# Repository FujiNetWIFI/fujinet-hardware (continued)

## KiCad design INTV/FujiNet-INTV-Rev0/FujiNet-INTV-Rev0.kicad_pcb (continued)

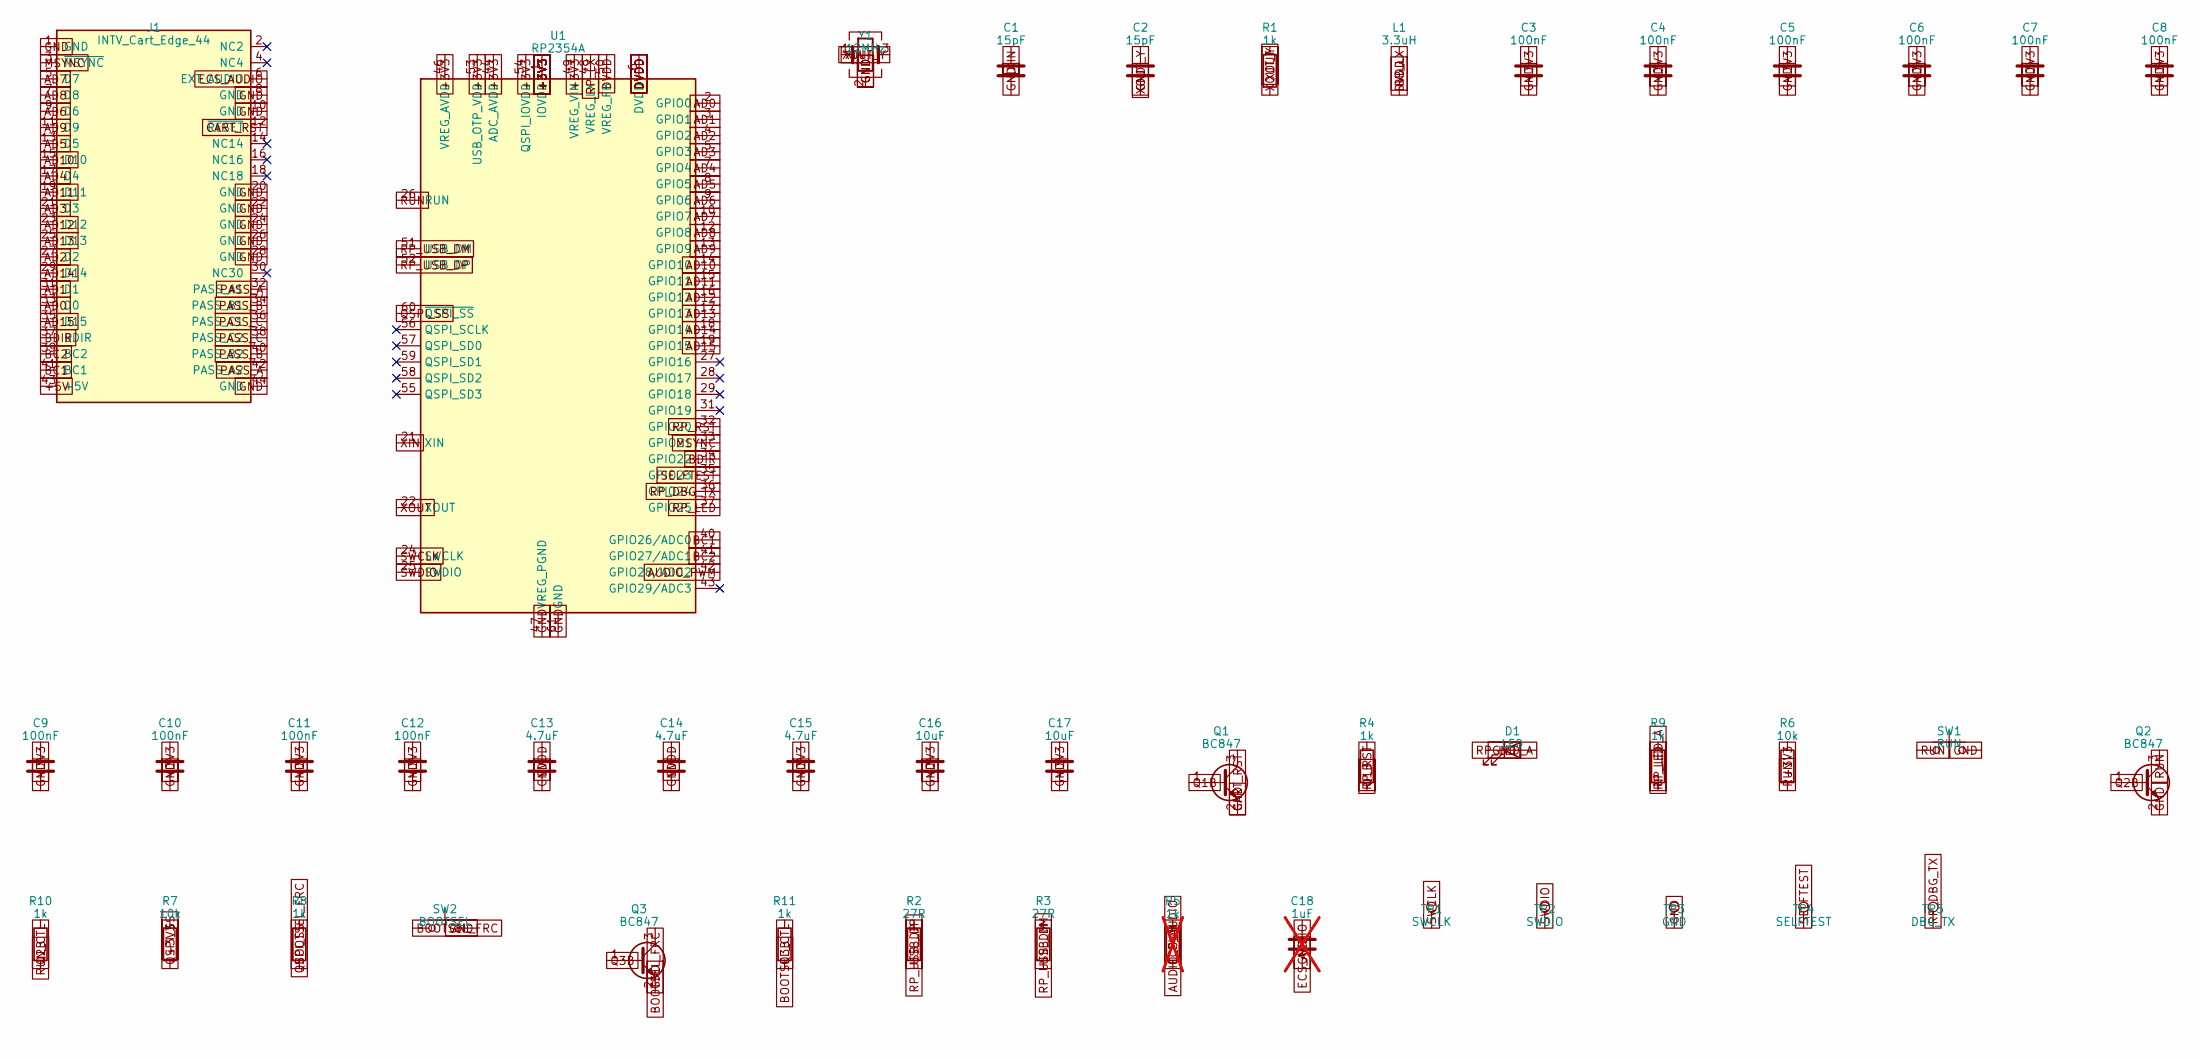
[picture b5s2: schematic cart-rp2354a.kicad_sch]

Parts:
C1, C2: 15pF; C_0603_1608Metric
C3, C4, C5, C6, C7, C8, C9, C10, C11, C12: 100nF; C_0603_1608Metric
C13, C14, C15: 4.7uF; C_0603_1608Metric
C16, C17: 10uF; C_0603_1608Metric; LCSC C19702
C18: 1uF; C_0603_1608Metric; not fitted
D1: LED; LED_0603_1608Metric
J1: INTV_Cart_Edge_44; MPN card edge, 2x22, 2.54mm
L1: 3.3uH; L_2016Metric; MPN AOTA-B201610S3R3-101-T; LCSC C42411119
Q1, Q2, Q3: BC847; SOT-23; LCSC C8598
R1, R4, R8, R9, R10, R11: 1k; R_0603_1608Metric
R2, R3: 27R; R_0603_1608Metric
R5: 1k; R_0603_1608Metric; not fitted
R6, R7: 10k; R_0603_1608Metric
SW1: RUN; SW_SPST_TL3342
SW2: BOOTSEL; SW_SPST_TL3342
TP1: SWCLK; TestPoint_Pad_D1.5mm
TP2: SWDIO; TestPoint_Pad_D1.5mm
TP3: GND; TestPoint_Pad_D1.5mm
TP4: SELFTEST; TestPoint_Pad_D1.5mm
TP5: DBG_TX; TestPoint_Pad_D1.5mm
U1: RP2354A; QFN-60-1EP_7x7mm_P0.4mm_EP3.4x3.4mm; MPN RP2354A; LCSC C41378174
Y1: 12MHz; Crystal_SMD_3225-4Pin_3.2x2.5mm; MPN ABM8-272-T3; LCSC C20625731

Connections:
+3V3: C3.1, C4.1, C5.1, C6.1, C7.1, C8.1, C9.1, C10.1, C11.1, C12.1, C15.1, C16.1, C17.1, R6.1, R7.1, U1.1 (IOVDD), U1.11 (IOVDD), U1.20 (IOVDD), U1.30 (IOVDD), U1.38 (IOVDD), U1.44 (ADC_AVDD), U1.45 (IOVDD), U1.46 (VREG_AVDD), U1.49 (VREG_VIN), U1.53 (USB_OTP_VDD), U1.54 (QSPI_IOVDD); also elsewhere on the board
+5V: J1.43 (+5V); also elsewhere on the board
AD0: J1.33 (D0), U1.2 (GPIO0)
AD1: J1.31 (D1), U1.3 (GPIO1)
AD2: J1.27 (D2), U1.4 (GPIO2)
AD3: J1.21 (D3), U1.5 (GPIO3)
AD4: J1.17 (D4), U1.7 (GPIO4)
AD5: J1.13 (D5), U1.8 (GPIO5)
AD6: J1.9 (D6), U1.9 (GPIO6)
AD7: J1.5 (D7), U1.10 (GPIO7)
AD8: J1.7 (D8), U1.12 (GPIO8)
AD9: J1.11 (D9), U1.13 (GPIO9)
AD10: J1.15 (D10), U1.14 (GPIO10)
AD11: J1.19 (D11), U1.15 (GPIO11)
AD12: J1.23 (D12), U1.16 (GPIO12)
AD13: J1.25 (D13), U1.17 (GPIO13)
AD14: J1.29 (D14), U1.18 (GPIO14)
AD15: J1.35 (D15), U1.19 (GPIO15)
AUDIO_PWM: R5.1, U1.42 (GPIO28/ADC2)
BC1: J1.41 (BC1), U1.40 (GPIO26/ADC0)
BC2: J1.39 (BC2), U1.41 (GPIO27/ADC1)
BDIR: J1.37 (BDIR), U1.34 (GPIO22)
BOOTSEL_CTL: R11.1; also elsewhere on the board
BOOTSEL_FRC: Q3.3 (C), R8.2, SW2.1
CART_RST: J1.12 (~RESET), Q1.3 (C)
DVDD: C13.1, C14.1, L1.2, U1.6 (DVDD), U1.23 (DVDD), U1.39 (DVDD), U1.50 (VREG_FB)
ECS_AUDIO: C18.1, J1.6 (EXT_AUDIO), R5.2
GND: C1.2, C2.2, C3.2, C4.2, C5.2, C6.2, C7.2, C8.2, C9.2, C10.2, C11.2, C12.2, C13.2, C14.2, C15.2, C16.2, C17.2, C18.2, D1.1 (K), J1.1 (GND), J1.8 (GND), J1.10 (GND), J1.20 (GND), J1.22 (GND), J1.24 (GND), J1.26 (GND), J1.28 (GND), J1.44 (GND), Q1.2 (E), Q2.2 (E), Q3.2 (E), SW1.2, SW2.2, TP3.1, U1.47 (VREG_PGND), U1.61 (GND), Y1.2 (G), Y1.4 (G); also elsewhere on the board
MSYNC: J1.3 (~MSYNC), U1.33 (GPIO21)
PASS_A: J1.32 (PASS_A1), J1.42 (PASS_A2)
PASS_B: J1.34 (PASS_B1), J1.40 (PASS_B2)
PASS_C: J1.36 (PASS_C1), J1.38 (PASS_C2)
Q1B: Q1.1 (B), R4.2
Q2B: Q2.1 (B), R10.2
Q3B: Q3.1 (B), R11.2
QSPI_SS: R7.2, R8.1, U1.60 (~QSPI_SS)
RP_DBG_TX: TP5.1, U1.36 (GPIO24)
RP_LED: R9.1, U1.37 (GPIO25)
RP_LED_A: D1.2 (A), R9.2
RP_LX: L1.1, U1.48 (VREG_LX)
RP_RST: R4.1, U1.32 (GPIO20)
RP_USB_DM: R3.1, U1.51 (USB_DM)
RP_USB_DP: R2.1, U1.52 (USB_DP)
RUN: Q2.3 (C), R6.2, SW1.1, U1.26 (RUN)
RUN_CTL: R10.1; also elsewhere on the board
SELFTEST: TP4.1, U1.35 (GPIO23)
SWCLK: TP1.1, U1.24 (SWCLK)
SWDIO: TP2.1, U1.25 (SWDIO)
USB_DM: R3.2; also elsewhere on the board
USB_DP: R2.2; also elsewhere on the board
XIN: C1.1, U1.21 (XIN), Y1.1
XOUT: R1.1, U1.22 (XOUT)
XOUT_Y: C2.1, R1.2, Y1.3

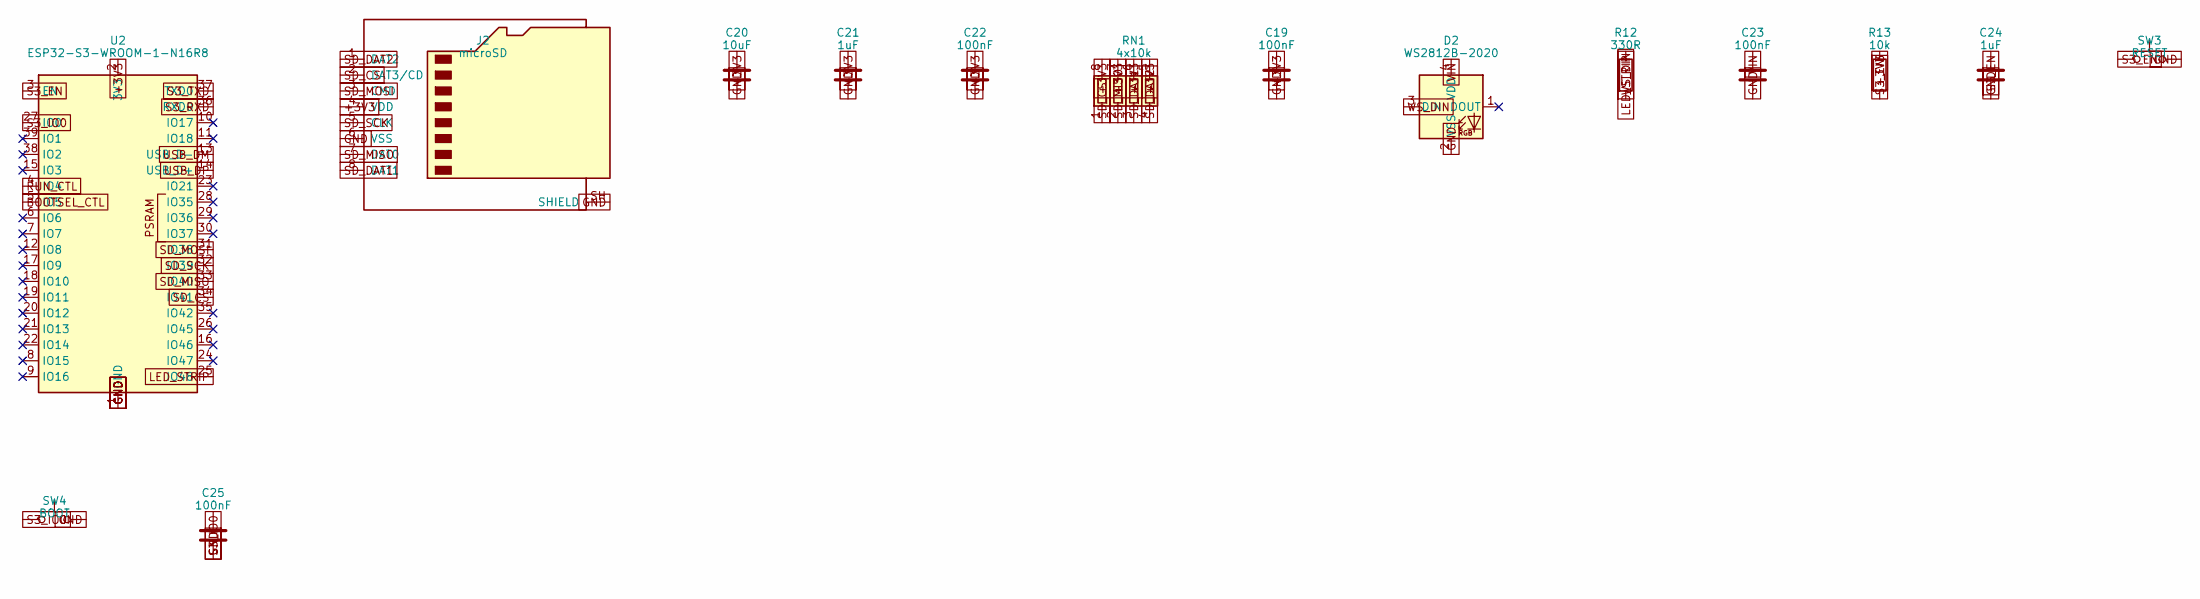
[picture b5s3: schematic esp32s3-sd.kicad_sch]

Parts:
C19, C22, C23, C25: 100nF; C_0603_1608Metric
C20: 10uF; C_0603_1608Metric; LCSC C19702
C21, C24: 1uF; C_0603_1608Metric
D2: WS2812B-2020; LED_WS2812B-2020_PLCC4_2.0x2.0mm; MPN WS2812B-2020; LCSC C5149201
J2: microSD; microSD_SUNTECH_ST-TF-003A; MPN SUNTECH ST-TF-003A
R12: 330R; R_0603_1608Metric
R13: 10k; R_0603_1608Metric
RN1: 4x10k; R_Array_Convex_4x0603
SW3: RESET; SW_SPST_TL3342
SW4: BOOT; SW_SPST_TL3342
U2: ESP32-S3-WROOM-1-N16R8; ESP32-S3-WROOM-1; MPN ESP32-S3-WROOM-1-N16R8; LCSC C2913202

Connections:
+3V3: C19.1, C20.1, C21.1, C22.1, J2.4 (VDD), R13.1, RN1.5 (R4.2), RN1.6 (R3.2), RN1.7 (R2.2), RN1.8 (R1.2), U2.2 (3V3); also elsewhere on the board
BOOTSEL_CTL: U2.5 (IO5); also elsewhere on the board
GND: C19.2, C20.2, C21.2, C22.2, C23.2, C24.2, C25.2, D2.2 (VSS), J2.6 (VSS), J2.SH (SHIELD), SW3.2, SW4.2, U2.1 (GND), U2.40 (GND), U2.41 (GND); also elsewhere on the board
LED_STRIP: R12.1, U2.25 (IO48)
RUN_CTL: U2.4 (IO4); also elsewhere on the board
S3_EN: C24.1, R13.2, SW3.1, U2.3 (EN); also elsewhere on the board
S3_IO0: C25.1, SW4.1, U2.27 (IO0); also elsewhere on the board
S3_RXD: U2.36 (RXD0); also elsewhere on the board
S3_TXD: U2.37 (TXD0); also elsewhere on the board
SD_CS: J2.2 (DAT3/CD), RN1.1 (R1.1), U2.34 (IO41)
SD_DAT1: J2.8 (DAT1), RN1.3 (R3.1)
SD_DAT2: J2.1 (DAT2), RN1.4 (R4.1)
SD_MISO: J2.7 (DAT0), RN1.2 (R2.1), U2.33 (IO40)
SD_MOSI: J2.3 (CMD), U2.31 (IO38)
SD_SCK: J2.5 (CLK), U2.32 (IO39)
USB_DM: U2.13 (USB_D-); also elsewhere on the board
USB_DP: U2.14 (USB_D+); also elsewhere on the board
VIN: C23.1, D2.4 (VDD); also elsewhere on the board
WS_DIN: D2.3 (DIN), R12.2

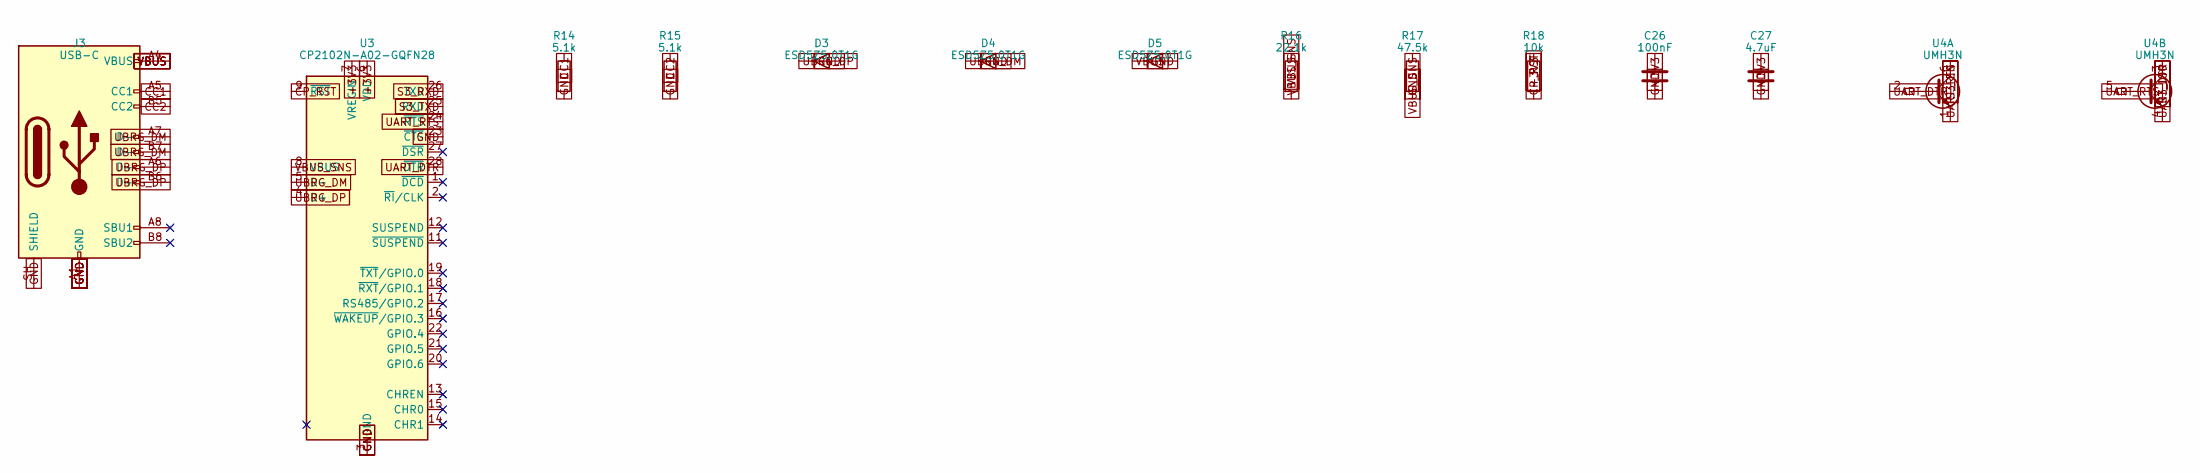
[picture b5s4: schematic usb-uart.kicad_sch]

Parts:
C26: 100nF; C_0603_1608Metric
C27: 4.7uF; C_0603_1608Metric
D3, D4, D5: ESD5Z5.0T1G; D_SOD-523; LCSC C316061
J3: USB-C; USB_C_Receptacle_HRO_TYPE-C-31-M-12; MPN HRO TYPE-C-31-M-12; LCSC C5178539
R14, R15: 5.1k; R_0603_1608Metric
R16: 22.1k; R_0603_1608Metric
R17: 47.5k; R_0603_1608Metric
R18: 10k; R_0603_1608Metric
U3: CP2102N-A02-GQFN28; QFN-28-1EP_5x5mm_P0.5mm_EP3.35x3.35mm; MPN CP2102N-A02-GQFN28R
U4: UMH3N; SOT-363_SC-70-6; LCSC C123008

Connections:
+3V3: C26.1, C27.1, R18.1, U3.6 (VDD), U3.7 (VREGIN); also elsewhere on the board
CC1: J3.A5 (CC1), R14.1
CC2: J3.B5 (CC2), R15.1
CP_RST: R18.2, U3.9 (~RST)
GND: C26.2, C27.2, D3.2 (A), D4.2 (A), D5.2 (A), J3.A1 (GND), J3.A12 (GND), J3.B1 (GND), J3.B12 (GND), J3.SH (SHIELD), R14.2, R15.2, R17.2, U3.3 (GND), U3.23 (~CTS), U3.29 (GND); also elsewhere on the board
S3_EN: U4.6 (C1); also elsewhere on the board
S3_IO0: U4.3 (C2); also elsewhere on the board
S3_RXD: U3.26 (TXD); also elsewhere on the board
S3_TXD: U3.25 (RXD); also elsewhere on the board
UART_DTR: U3.28 (~DTR), U4.2 (B1), U4.4 (E2)
UART_RTS: U3.24 (~RTS), U4.1 (E1), U4.5 (B2)
UBRG_DM: D4.1 (K), J3.A7 (D-), J3.B7 (D-), U3.5 (D-)
UBRG_DP: D3.1 (K), J3.A6 (D+), J3.B6 (D+), U3.4 (D+)
VBUS: D5.1 (K), J3.A4 (VBUS), J3.A9 (VBUS), J3.B4 (VBUS), J3.B9 (VBUS), R16.1; also elsewhere on the board
VBUS_SNS: R16.2, R17.1, U3.8 (VBUS)

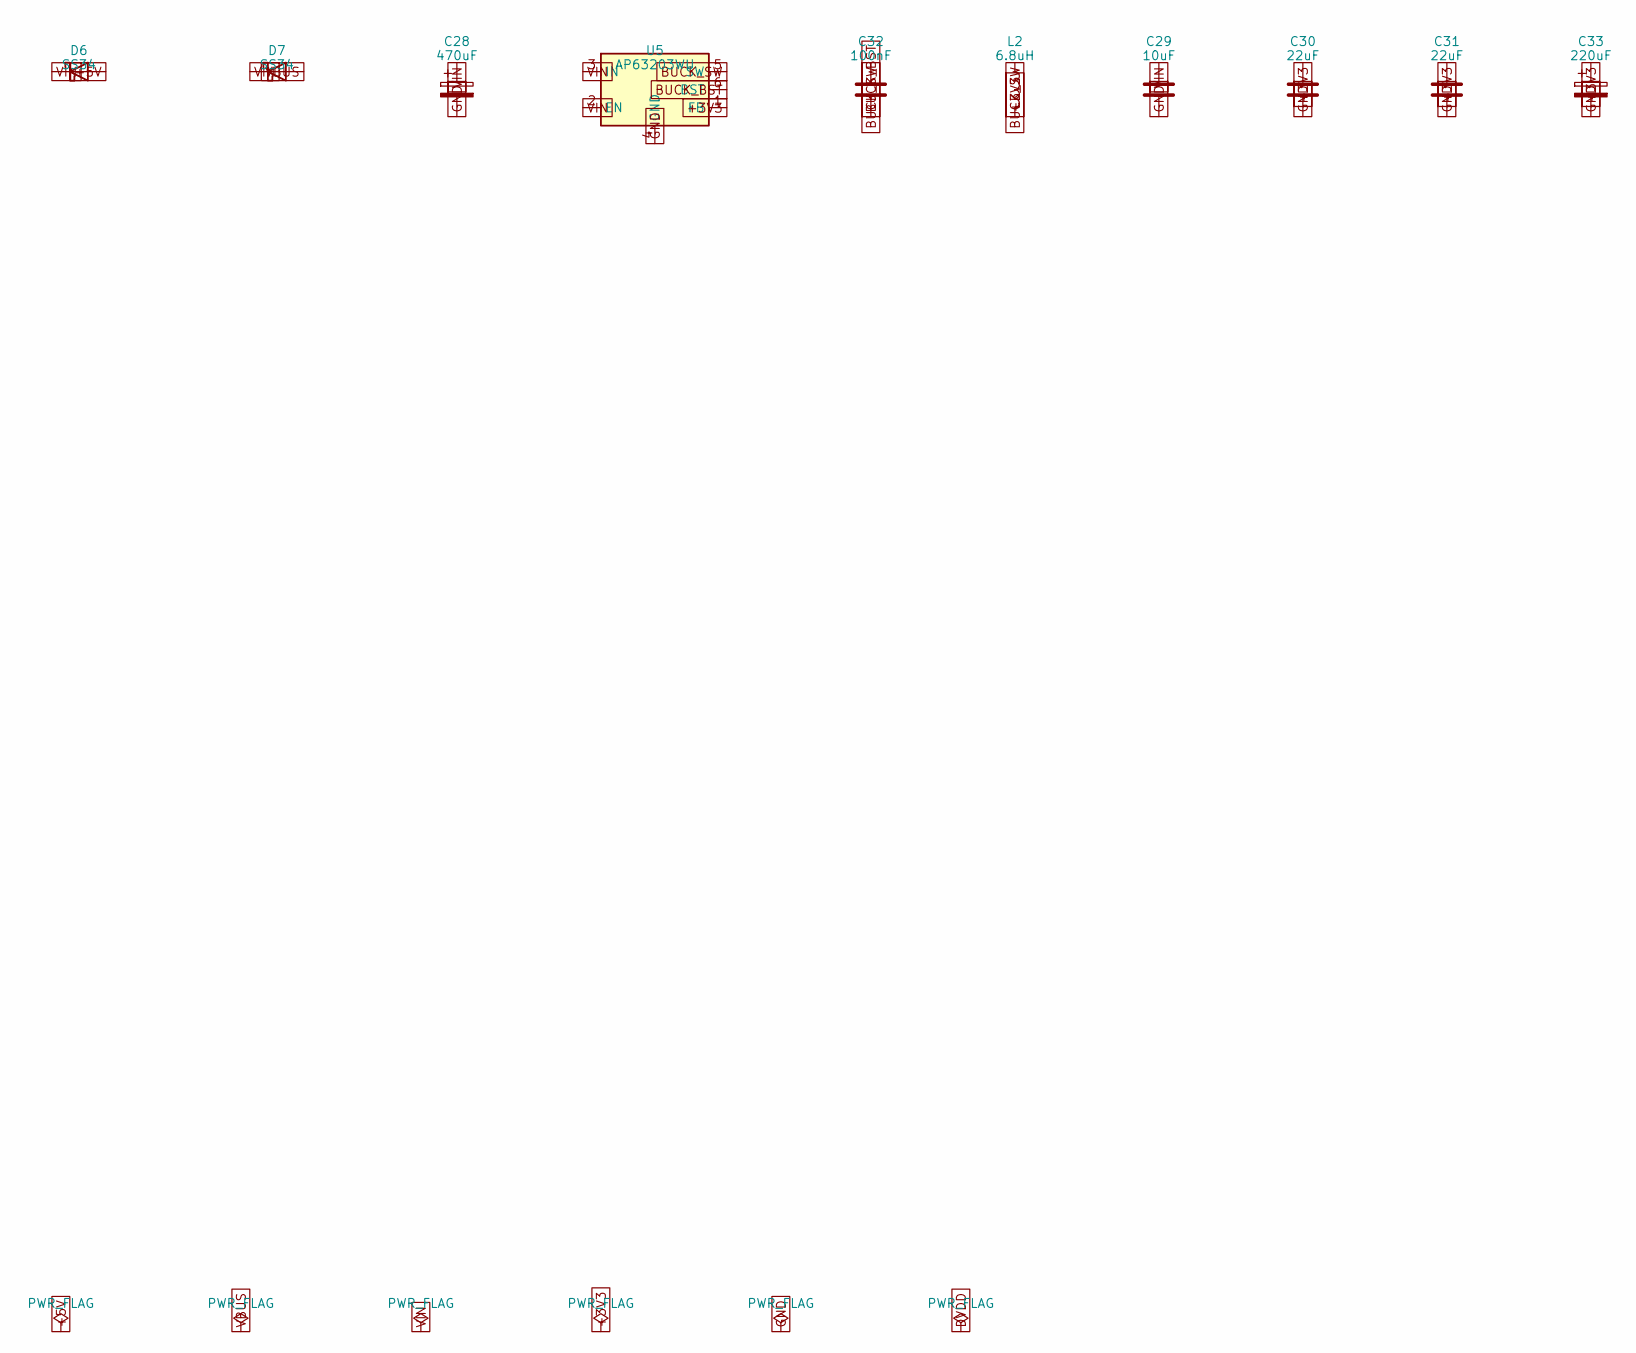
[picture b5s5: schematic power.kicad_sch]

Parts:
C28: 470uF; CP_EIA-7343-31_Kemet-D; MPN 6.3V polymer, 7343
C29: 10uF; C_0805_2012Metric
C30, C31: 22uF; C_0805_2012Metric; LCSC C45783
C32: 100nF; C_0603_1608Metric
C33: 220uF; CP_EIA-7343-31_Kemet-D; MPN 6.3V polymer, 7343
D6, D7: SS34; D_SMA; LCSC C8678
L2: 6.8uH; L_Sunlord_SWPA4030S; MPN 6.8uH >=2.5A shielded 4030
U5: AP63203WU; TSOT-23-6; MPN AP63203WU-7; LCSC C965680

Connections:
+3V3: C30.1, C31.1, C33.1, L2.2, U5.1 (FB); also elsewhere on the board
+5V: D6.2 (A); also elsewhere on the board
BUCK_BST: C32.2, U5.6 (BST)
BUCK_SW: C32.1, L2.1, U5.5 (SW)
GND: C28.2, C29.2, C30.2, C31.2, C33.2, U5.4 (GND); also elsewhere on the board
VBUS: D7.2 (A); also elsewhere on the board
VIN: C28.1, C29.1, D6.1 (K), D7.1 (K), U5.2 (EN), U5.3 (IN); also elsewhere on the board

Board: 4 copper layers, 84 parts (5 on the bottom side), 77 nets, no tracks yet.

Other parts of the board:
H1, H2: MountingHole_5.4mm_NPTH

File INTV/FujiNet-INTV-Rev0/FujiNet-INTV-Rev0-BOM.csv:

"Refs","Value","Footprint","MPN","LCSC","Description","DNP"
"C1,C2","15pF","FujiNet-INTV:C_0603_1608Metric","","","crystal load",""
"C3,C4,C5,C6,C7,C8,C9,C10,C11,C12,C19,C22,C23,C25,C26,C32","100nF","FujiNet-INTV:C_0603_1608Metric","","","IO0 debounce,SD VDD decoupling,U1 decoupling,U2 decoupling,U3 decoupling,WS2812 decoupling,bootstrap",""
"C13,C14,C15,C27","4.7uF","FujiNet-INTV:C_0603_1608Metric","","","DVDD bulk,U3 bulk,VREG_VIN bulk",""
"C16,C17,C20","10uF","FujiNet-INTV:C_0603_1608Metric","","C19702","3V3 bulk near U1,U2 bulk",""
"C18","1uF","FujiNet-INTV:C_0603_1608Metric","","","ECS audio filter (DNP)","DNP"
"C21,C24","1uF","FujiNet-INTV:C_0603_1608Metric","","","EN reset delay,U2 decoupling",""
"C28","470uF","FujiNet-INTV:CP_EIA-7343-31_Kemet-D","6.3V polymer, 7343","","VIN bulk",""
"C29","10uF","FujiNet-INTV:C_0805_2012Metric","","","buck input",""
"C30,C31","22uF","FujiNet-INTV:C_0805_2012Metric","","C45783","buck output",""
"C33","220uF","FujiNet-INTV:CP_EIA-7343-31_Kemet-D","6.3V polymer, 7343","","3V3 bulk (S3 WiFi bursts)",""
"D1","LED","FujiNet-INTV:LED_0603_1608Metric","","","RP activity LED (light pipe)",""
"D2","WS2812B-2020","FujiNet-INTV:LED_WS2812B-2020_PLCC4_2.0x2.0mm","WS2812B-2020","C5149201","status LED (fujiversal LED_STRIP, 1px)",""
"D3,D4,D5","ESD5Z5.0T1G","FujiNet-INTV:D_SOD-523","","C316061","ESD, USB D+,ESD, USB D-,ESD, VBUS",""
"D6,D7","SS34","FujiNet-INTV:D_SMA","","C8678","USB VBUS OR-ing,console 5V OR-ing / backfeed block",""
"J1","INTV_Cart_Edge_44","FujiNet-INTV:INTV_Cart_Edge_44","card edge, 2x22, 2.54mm","","Intellivision cartridge edge (geometry per PiNTY CARD)",""
"J2","microSD","FujiNet-INTV:microSD_SUNTECH_ST-TF-003A","SUNTECH ST-TF-003A","","push-push microSD (footprint per CoCo-FujiNet-Rev0000)",""
"J3","USB-C","FujiNet-INTV:USB_C_Receptacle_HRO_TYPE-C-31-M-12","HRO TYPE-C-31-M-12","C5178539","USB-C 16P (UART/flash port)",""
"L1","3.3uH","FujiNet-INTV:L_2016Metric","AOTA-B201610S3R3-101-T","C42411119","RP2354A core VREG inductor",""
"L2","6.8uH","FujiNet-INTV:L_Sunlord_SWPA4030S","6.8uH >=2.5A shielded 4030","","buck inductor (AP63203 datasheet)",""
"Q1,Q2,Q3","BC847","FujiNet-INTV:SOT-23","","C8598","BOOTSEL force (S3 GPIO5, Hi-Z idle),RUN force (S3 GPIO4, Hi-Z idle),console /RESET open-collector",""
"R1,R4,R8,R9,R10,R11","1k","FujiNet-INTV:R_0603_1608Metric","","","BOOTSEL series,LED series,Q1 base,Q2 base,Q3 base,XOUT series (RP2350 design guide)",""
"R2,R3","27R","FujiNet-INTV:R_0603_1608Metric","","","USB D+ series,USB D- series",""
"R5","1k","FujiNet-INTV:R_0603_1608Metric","","","ECS audio PWM series (DNP)","DNP"
"R6,R7,R13,R18","10k","FujiNet-INTV:R_0603_1608Metric","","","CP2102N /RST pull-up,EN pull-up,QSPI_SS/BOOTSEL pull-up,RUN pull-up",""
"R12","330R","FujiNet-INTV:R_0603_1608Metric","","","WS2812 data series",""
"R14,R15","5.1k","FujiNet-INTV:R_0603_1608Metric","","","CC1 pull-down (UFP),CC2 pull-down (UFP)",""
"R16","22.1k","FujiNet-INTV:R_0603_1608Metric","","","VBUS sense divider hi",""
"R17","47.5k","FujiNet-INTV:R_0603_1608Metric","","","VBUS sense divider lo",""
"RN1","4x10k","FujiNet-INTV:R_Array_Convex_4x0603","","","SD pull-ups",""
"SW1","RUN","FujiNet-INTV:SW_SPST_TL3342","","","RP2354A reset button",""
"SW2","BOOTSEL","FujiNet-INTV:SW_SPST_TL3342","","","RP2354A BOOTSEL button",""
"SW3","RESET","FujiNet-INTV:SW_SPST_TL3342","","","ESP32 reset button",""
"SW4","BOOT","FujiNet-INTV:SW_SPST_TL3342","","","ESP32 IO0 boot button",""
"U1","RP2354A","FujiNet-INTV:QFN-60-1EP_7x7mm_P0.4mm_EP3.4x3.4mm","RP2354A","C41378174","RP2350A + 2MB stacked QSPI flash, QFN-60",""
"U2","ESP32-S3-WROOM-1-N16R8","FujiNet-INTV:ESP32-S3-WROOM-1","ESP32-S3-WROOM-1-N16R8","C2913202","16MB QIO flash / 8MB octal PSRAM (IO35-37 NC)",""
"U3","CP2102N-A02-GQFN28","FujiNet-INTV:QFN-28-1EP_5x5mm_P0.5mm_EP3.35x3.35mm","CP2102N-A02-GQFN28R","","USB-UART bridge (DevKitC-1 UART port)",""
"U4","UMH3N","FujiNet-INTV:SOT-363_SC-70-6","","C123008","auto-program: DTR/RTS -> EN/IO0 (DevKitC-1 circuit)",""
"U5","AP63203WU","FujiNet-INTV:TSOT-23-6","AP63203WU-7","C965680","3.3V/2A sync buck (FB tied to VOUT: fixed 3.3V version)",""
"Y1","12MHz","FujiNet-INTV:Crystal_SMD_3225-4Pin_3.2x2.5mm","ABM8-272-T3","C20625731","12MHz 3225, CL=10pF (per PiNTY)",""

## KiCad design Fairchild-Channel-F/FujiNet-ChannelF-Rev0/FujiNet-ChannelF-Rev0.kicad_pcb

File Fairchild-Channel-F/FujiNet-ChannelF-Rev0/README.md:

# FujiNet-ChannelF Rev0

FujiNet for the Fairchild Channel F: an RP2040 Videocart that serves the F8 bus, plus an ESP32-S3
(the FujiNet, the RP2040's USB host), on one cartridge.

**Status (2026-10-11): laid out, routed and packaged for JLCPCB. Not yet built.** The RP2040
firmware (`fujichannelf` in `fujinet-firmware/pico/channelf/`) runs unchanged. Read *Before
ordering* first.

| | |
|---|---|
| Board | 4 layers, 1.6 mm, 77 x 131.5 mm: the outline of aotta's PicoVideocart, which fits a real console and an original Videocart shell |
| Edge | 22 hard-gold fingers on the bottom face (B.Cu), 2.54 mm, key slot between pins 11 and 12 |
| Parts | 99 in the schematic: 86 placed by JLCPCB on the top face, 12 bare-copper test pads, and the edge itself |
| Fab package | `exports/jlcpcb/`: gerbers + drill, BOM, CPL with measured rotations, `ORDER-JLCPCB.md` |
| Shell | `case/board-anchors.scad`: everything a printed shell needs from the board |

See `docs/floorplan-study.md` for how the board was laid out, and `docs/design-review-rev0.md`
for the kicad-happy design review.

| Sheet | Contents |
|---|---|
| root | Block diagram. Every connection between sheets is a drawn wire. |
| `cart-rp` (A2) | 22-contact edge → 2x SN74LVC4245A → RP2040 (one symbol), plus the RP2040's own circuit: supplies, 2 MB QSPI flash, 12 MHz crystal, SWD, RUN / BOOTSEL / RESET, USB to the S3 |
| `fujinet` | ESP32-S3-WROOM-1-N16R8, microSD, WS2812B status LED, S3 EN / BOOT buttons |
| `usb` | USB-C, CP2102N bridge and esptool auto-program pair (UMH3N) for flashing the S3 |
| `power` | Console 5 V and USB VBUS diode-ORed into +5V; AP63203 buck to +3V3 (S3 side); AP2112K LDO to +3V3_RP (RP side) |

Every sheet is fully wired: each net is one drawn piece, and labels only name wires or leave the
sheet. Two sheets have one wire crossing each. On `cart-rp`, WRITE's scope pad drops past PHI's
line. On `usb`, it is the auto-program pair, as on the Astrocade. The control
translator's channels follow the board's order (see *The board*).

## Firmware contract

`tools/check_nets.py` checks this against the firmware itself; it does not read `design.py`.

| Signal | Edge pin | RP2040 | Source |
|---|---|---|---|
| D0-D7 | 3, 4, 9, 11, 14, 16, 17, 18 | GPIO0-7, through U8 | `channelf_cart.h` `D0_PIN` |
| ROMC0-4 | 6, 7, 8, 10, 12 | GPIO8-12, through U9 | `ROMC0_PIN` |
| WRITE / PHI | 15 / 13 | GPIO13 / GPIO14, through U9 | `WRITE_PIN`, `PHI_PIN` |
| DIR | n/a | GPIO15 → U8 DIR (1 = console → cart, 0 = cart drives) | `DIR_PIN`, `channelf_cart.c` |
| /INTREQ | 5 | GPIO16 → Q1 (2N7002) open drain (never driven) | `INTREQ_PIN` |
| LED | n/a | GPIO25 | stock `boards/pico.h` |
| +5V / GND / NC / +12V | 19-20 / 1-2 / 21 / 22 | +12V and NC left open | |

The edge pinout comes from Fairchild's FVE100 schematic (J5) and the
[channelf.se veswiki Pinouts](https://channelf.se/veswiki/index.php?title=Pinouts) page.

S3 pins follow `include/pinmap/fujiversal-channelf.h` on the `fujiversal-channelf-board` branch:

- microSD: IO38-41, card detect on IO42
- WS2812: IO48
- UART0: 43 / 44
- USB host to the RP: IO19 / IO20

RP2040 RUN and BOOTSEL are driven from S3 IO4 and IO5, the same pins as on the Astrocade board.
**That pinmap does not declare `PIN_RP2040_RUN` / `PIN_RP2040_BOOTSEL` yet**; `check_nets.py`
reports it as a warning.

## Why two SN74LVC4245A

- **The F3850's data bus needs VIH 2.9 V minimum** (F3850 data sheet, Table 7). A 3.3 V driver
  has almost no margin, whether a bare RP pin or a 74LVC245A at 3.3 V. The RP2040 is also not
  5 V tolerant (VPIN max = IOVDD + 0.5 V).
- **The '4245A's A port runs at 5 V with TTL inputs** (VIH 2.0 V).
  - The console's outputs give 3.9 V on DB / ROMC and 4.4 V on WRITE / PHI.
  - The A port drives at least 4.3 V back onto the bus at VCCA 4.5 V: 1.4 V above the F3850's
    2.9 V.
- **DIR high = A → B.** With A on the console side, that is the firmware's own polarity: no
  inverter, no firmware change.
- **DIR and /OE are TTL inputs referenced to VCCA**, so the RP's 3.3 V drives them correctly.
- **R18, 4.7k to +3V3_RP, holds U8's DIR high** through RP reset and boot. Without it, the
  RP2040's 50-80 kΩ pad pull-down would read 0, and the cart would drive the bus while the BIOS
  runs.
- **VCCA is CONS_5V, taken straight off edge pins 19 / 20, ahead of the OR diode.** With the
  console off, VCCA drops below 100 mV and both translators go high-Z (TI SCAS375K §7.5, plus
  Ioff). A USB-powered cart therefore cannot back-power the console through the bus. The
  firmware's DIR = 1 idle is the second line of defence.
- **U9 carries the control lines, console → RP only**: DIR is tied to VCCA and /OE to GND. Its
  channels run ROMC0-4, WRITE, PHI. Its spare A8 is held low through R20, 10k (SCAS375K 5.4
  note 1), and B8 is left open.

`tools/audit/margins.py` computes every one of these margins.

## The Videocart edge

All 22 contacts are on **one face, the one that is down in the console**: the console's spring
contacts push up from below.

- This board puts them on **B.Cu** and every part on F.Cu, which faces up (toward the label).
- Pitch 2.54 mm: pins 1-11, a 4-pitch gap holding the key slot, pins 12-22.
- Seen from the parts side with the edge toward you, pin 1 (GND) is on the left. Seen from the
  contact side, it is on the right.

| | |
|---|---|
| Fingers | 1.8 mm wide, copper 0.5-12.0 mm from the edge, hard gold, 30-45° bevel |
| Key slot | 1.651 x 12.58 mm, round top, 6.1 mm lead-in (aotta's, proven on a console) |
| Tab | 68.3 mm wide, straight for 30 mm: no parts on it |
| Body | 77 mm after a 45° taper; 131.5 mm overall; four 5.6 mm holes on the original shell's bosses |
| Pins 21 / 22 | Spare and +12 V: bare fingers, nothing within 1 mm |

Sources, transcribed and checked by `tools/audit/edge_orientation.py`:

- Andrea Ottaviani's aotta/PicoVideocart (GPL-3.0), its fab gerbers: the outline, the key slot,
  the shell holes, the thickness and the finger order. It works in a console. Its footprint
  numbers its pads in reverse.
- timtashpulatov/fart's `Cart_Conn` footprint.
- US 4,095,791.
- The veswiki photo of a real cart's contact face.

Numbers only: no file from these sources is in this repository. The board is CERN-OHL-W-2.0.

The original thickness, the console key's width and the console connector's reach are documented
nowhere. That is why the tab carries no parts, and why `docs/tab-overlay-1to1.pdf` exists.

## The board

`docs/floorplan-study.md` has the whole story. In short:

- **The bus.** The two translators stand side by side over the bus fingers, with U8 (data) on the
  west. The RP2040 sits straight north of them at rotation 90, its GP0-GP14 along its south side
  and up its east side. With U9's channels in the board's order, translator → RP crosses nothing.
- **The RP2040's ring** started from the routed `atari2600-rev0` board's and was then measured and
  improved:
  - VREG_VOUT, DVDD and VREG_VIN reach their capacitors on F.Cu with no via;
  - the USB 27R sit in line right off the pins;
  - XOUT and the bus-side IOVDD pins drop through vias in the ring's free band.
- **Power.**
  - The AP63203's input loop closes on F.Cu: its three input capacitors are stacked under VIN and
    GND.
  - The AP2112K stands on the In2 island boundary: input in +5V, output in +3V3_RP.
  - The console's 5 V enters on fingers 19 / 20 into a CONS_5V island under the translators.
- **The grip end** stays outside the console. The ESP32-S3's antenna sits flush with it, over a
  copper-free keep-out on every layer, beside the microSD and the USB-C. RESET (SW1) and both LEDs
  are just inside. The USB-C's shell face stands 0.45 mm past the edge (HRO's recommended PCB-edge
  position) and the microSD's face 0.5 mm inside it.
- **Connector alignment (2026-10-13).** The USB-C (J2) moved 1.8 mm to HRO's recommended PCB-edge
  position (its face had sat 1.35 mm inside the board, where a plug's overmold meets the PCB edge),
  and the microSD / USB-C 3D models were re-seated on their footprints; DRC still 0 / 0 / 0 (design
  review, "Post-layout change").
- **Stack-up** JLC04161H-7628: F.Cu signal / In1 GND / In2 power islands / B.Cu signal.

## Build

```
tools/build_all.sh              # schematic, ERC, firmware checks, re-link + DRC the routed board, exports, fab gates
LAYOUT=1 tools/build_all.sh     # ... and re-place, re-route the board from scratch (~25 min, Freerouting)
```

It runs, in order:

1. `harvest_symbols.py`, `make_edge_fp.py`, `make_fp_extra.py`, `audit/edge_orientation.py`
2. `gen_sch.py`: drawing checks, hierarchy, netlist parity with `design.py`
3. KiCad ERC at all severities
4. `check_nets.py`
5. One of:
   - with `LAYOUT=1`: `gen_pcb.py` (placement, planes, locked support copper, fan-out) and
     `route_board.sh` (Freerouting, the grid finisher, clean-up, stitching, DRC gate);
   - otherwise: `sync_pcb_sheets.py` and DRC with schematic parity.
6. `export.py`: BOMs, schematic PDF, the JLCPCB package, layout views
7. `tab_overlay.py` and `audit/check_fab.py` (which runs `audit/check_gerbers.py`)

The circuit lives in `tools/design.py`, the drawing in `tools/sch_layout.py`, the floorplan in
`tools/placement.py` and the edge in `tools/edge_geom.py`. Never edit the generated `.kicad_*`
files. `tools/refs.lock` freezes the geographic references and `tools/nets.lock` the net names.

`check_nets.py` reads the firmware from `$FUJINET_FIRMWARE` (default
`~/Workspace/fujinet-firmware`) and the pico-sdk from `$PICO_SDK_PATH` (default
`/usr/share/pico-sdk`).

The audits:

| Command | What it checks |
|---|---|
| `tools/audit/run_sch_audit.sh` | kicad-happy schematic analysis, SPICE |
| `tools/audit/run_pcb_audit.sh` | PCB, cross-domain, EMC, thermal, gerbers, release gate |
| `tools/audit/margins.py` | Circuit margins |
| `tools/audit/layout_checks.py` | The layout's datasheet claims, measured on the copper |
| `tools/audit/make_deep_review.py` + `deep_review_gate.py` | Per-IC datasheet review |
| `tools/audit/sourcing.py` | JLC / LCSC stock |
| `tools/audit/jlc/measure_rotations.py` | CPL rotations against the EasyEDA footprints |

## Verification

2026-10-11, the board built by `LAYOUT=1 tools/build_all.sh`:

| Check | Result |
|---|---|
| KiCad ERC, all severities | 0 |
| Netlist parity with `design.py` | 87 nets match |
| `tools/check_nets.py` (netlist vs the firmware) | 204 checks, 0 failed, 1 warning (the pin map lacks `PIN_RP2040_RUN` / `_BOOTSEL`: open item 1) |
| `tools/audit/edge_orientation.py` | every check against aotta, fart and the veswiki numbers |
| KiCad DRC, schematic parity, all severities | 0 violations, 0 unconnected, 0 parity issues |
| `tools/check_vias.py` | 756 vias, none in a foreign pad (758 before the connector alignment below) |
| `tools/audit/layout_checks.py` | 9 / 9: decoupling, the buck's loop, crystal, exposed-pad vias, USB skew, antenna keep-out |
| `tools/audit/margins.py` | all positive |
| `tools/audit/check_fab.py` + `check_gerbers.py` | 10 / 10; every gerber check |
| JLC CPL rotations | measured for all 35 (footprint, LCSC) pairs |
| `tools/audit/sourcing.py` | 38 / 38 lines in JLCPCB stock for 5 boards; 37 "normal" at LCSC |
| kicad-happy | SPICE 15 / 15; thermal 100; EMC 40 (no critical); deep review 24 / 24 verified; `fab_release_gate --strict` 10 pass, 2 waived |
| Pinouts | every part with more than two pins, and every polarized part, against its datasheet: no mismatch |

`docs/design-review-rev0.md` has the full review: the triage, the waivers and two open questions.

## Before ordering

1. **The edge.** Print `docs/tab-overlay-1to1.pdf` at 100 % (no fit-to-page) and check its 50 mm
   ruler. Lay a real Videocart board on it, contacts up, edge toward you. These must match:
   - the 22 contacts in two groups of 11;
   - the key slot;
   - the 68.3 mm tab;
   - the 5.6 mm holes on the bosses.
2. **Stock.** Re-run `python3 tools/audit/sourcing.py`. On 2026-10-11 every line was in stock for
   5 boards (`docs/sourcing.md`). The thinnest lines are the TL3342 buttons (1.5k) and the
   W25Q16 (1.5k).
3. **The order.** Follow `exports/jlcpcb/ORDER-JLCPCB.md`:
   - 4 layers, ENIG, hard-gold beveled fingers;
   - Standard PCBA, top side;
   - check the placement preview, especially the parts whose CPL rotation is only medium
     confidence (the TL3342 buttons, the BAT54C, the USB-C).

## Open items

**Circuit, for a decision** (`docs/design-review-rev0.md`, *Open questions*). Both are left as
drawn:

- the USB D+ / D- protection: 80 pF ESD5Z parts, where the CP2102N's datasheet shows a
  low-capacitance USB array;
- the CP2102N's RSTb pull-up: 10k, where the datasheet recommends 1k.

**Firmware, not changed by this work:**

1. Add `PIN_RP2040_RUN GPIO_NUM_4` and `PIN_RP2040_BOOTSEL GPIO_NUM_5` to
   `fujiversal-channelf.h`, and drop its PROVISIONAL note.
2. The "'245" comments in `channelf_cart.h` should say SN74LVC4245A.

**Bring-up:**

3. Scope the WRITE edge and the write-data timing (PROVISIONAL in `channelf_cart.c`):
   - TP10 (WRITE), TP11 (PHI) and TP12 (DIR);
   - TP2 (GP17) is a spare for a firmware scope trigger;
   - SWD is on TP6 (SWCLK), TP5 (SWDIO), TP7 (GND) and TP4 (RUN), for the first flash with a Debug
     Probe.
4. Console +5V headroom with Wi-Fi bursts (~400 mA peak) is unmeasured. Measure CONS_5V at the
   fingers. If the console rail sags, run the cart from USB-C.
5. Older SN74LVC4245A dies may predate the Ioff / VCC-isolation spec (datasheet revision K). If
   so, the firmware's DIR = 1 idle still keeps U8 from driving the bus.
6. Getting back to CONFIG after booting a Videocart: press RESET (SW1, which resets the RP and
   the S3), then the console's reset. The cart edge has no reset line.
7. **The shell.** `case/board-anchors.scad` has the outline, slot, bosses, buttons, LEDs, USB-C,
   microSD and antenna positions. The board's height inside the shell has to match the console's
   slot; that is unmeasured.

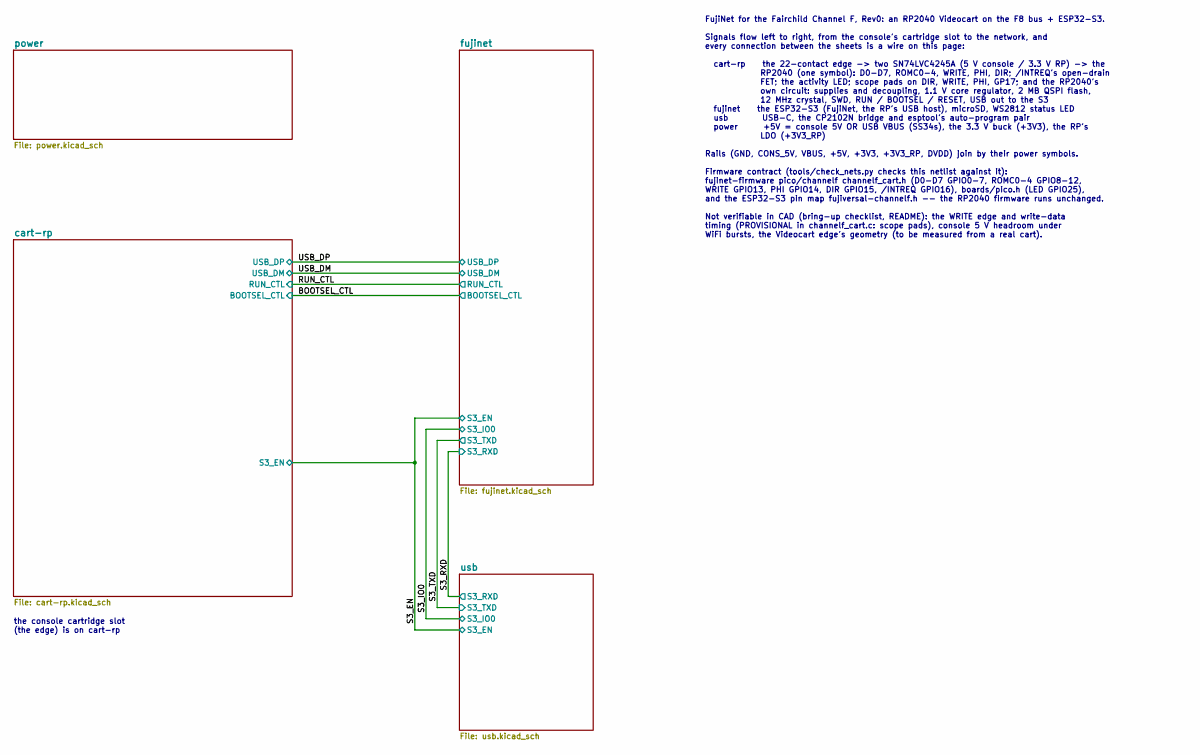
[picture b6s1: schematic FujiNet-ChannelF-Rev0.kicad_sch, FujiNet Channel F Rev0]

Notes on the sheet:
the console cartridge slot (the edge) is on cart-rp
FujiNet for the Fairchild Channel F, Rev0: an RP2040 Videocart on the F8 bus + ESP32-S3. Signals flow left to right, from the console's cartridge slot to the network, and every connection between the sheets is a wire on this page: cart-rp the 22-contact edge -> two SN74LVC4245A (5 V console / 3.3 V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

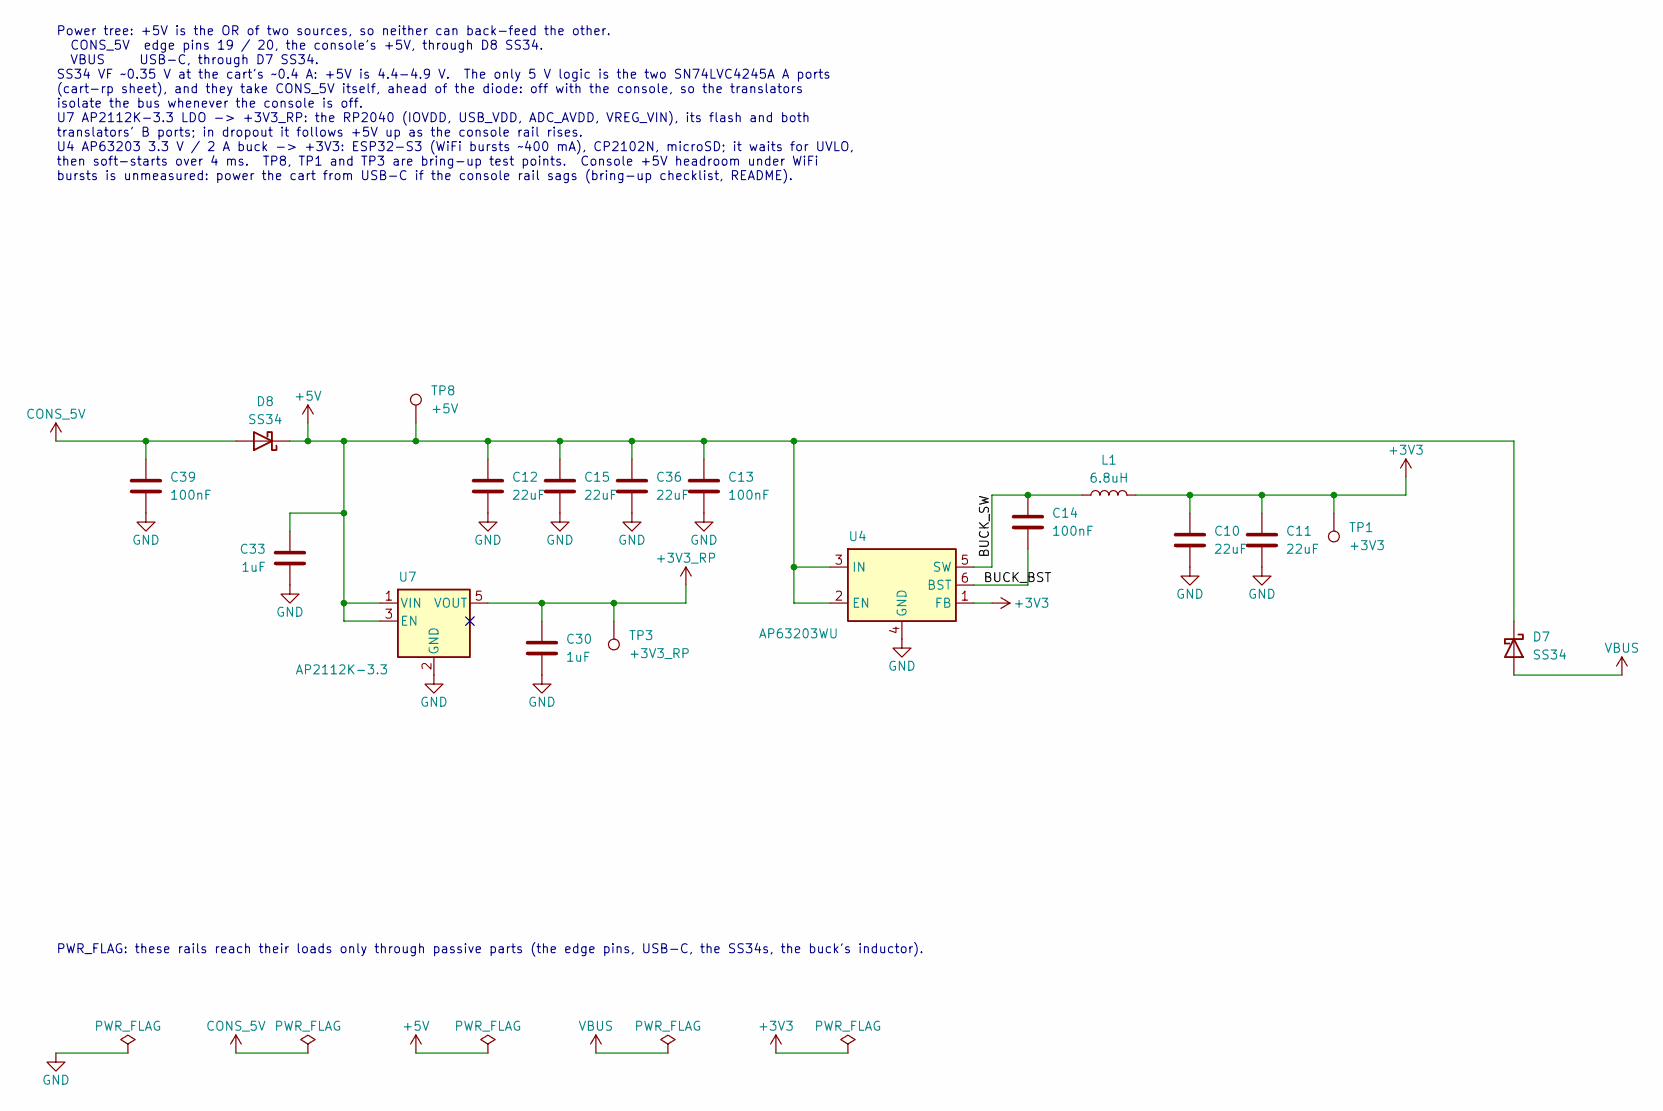
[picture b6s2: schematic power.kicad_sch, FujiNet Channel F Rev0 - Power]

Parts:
C10, C11, C12, C15, C36: 22uF; C_0805_2012Metric; MPN CL21A226MAQNNNE; LCSC C45783
C13, C14, C39: 100nF; C_0603_1608Metric; MPN CC0603KRX7R9BB104; LCSC C14663
C30, C33: 1uF; C_0603_1608Metric; MPN CL10A105KB8NNNC; LCSC C15849
D7, D8: SS34; D_SMA; MPN SS34; LCSC C8678
L1: 6.8uH; L_Sunlord_SWPA4030S; MPN SWPA4030S6R8MT; LCSC C62684
TP1: +3V3; TestPoint_Pad_D1.5mm
TP3: +3V3_RP; TestPoint_Pad_D1.5mm
TP8: +5V; TestPoint_Pad_D1.5mm
U4: AP63203WU; TSOT-23-6; MPN AP63203WU-7; LCSC C780769
U7: AP2112K-3.3; SOT-23-5; MPN AP2112K-3.3TRG1; LCSC C51118

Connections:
+3V3: C10.1, C11.1, L1.2, TP1.1, U4.1 (FB); also elsewhere on the board
+3V3_RP: C30.1, TP3.1, U7.5 (VOUT); also elsewhere on the board
+5V: C12.1, C13.1, C15.1, C33.1, C36.1, D7.1 (K), D8.1 (K), TP8.1, U4.2 (EN), U4.3 (IN), U7.1 (VIN), U7.3 (EN); also elsewhere on the board
/power/BUCK_BST: C14.2, U4.6 (BST)
/power/BUCK_SW: C14.1, L1.1, U4.5 (SW)
CONS_5V: C39.1, D8.2 (A); also elsewhere on the board
GND: C10.2, C11.2, C12.2, C13.2, C15.2, C30.2, C33.2, C36.2, C39.2, U4.4 (GND), U7.2 (GND); also elsewhere on the board
VBUS: D7.2 (A); also elsewhere on the board

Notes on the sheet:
PWR_FLAG: these rails reach their loads only through passive parts (the edge pins, USB-C, the SS34s, the buck's inductor).
Power tree: +5V is the OR of two sources, so neither can back-feed the other. CONS_5V edge pins 19 / 20, the console's +5V, through D8 SS34. VBUS USB-C, through D7 SS34. SS34 VF ~0.35 V at the cart's ~0.4 A: +5V is 4.4-4.9 V. The only 5 V logic is the two SN74LVC4245A A ports (cart-rp sheet), and t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
